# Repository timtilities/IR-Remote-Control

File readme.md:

I have a *Hunter* space heater whose remote control had partially stopped working. The power and mode buttons no longer functioned. Rather than buying a new heater, I decided to take a crack at making a new remote control for it.

***

Some of the buttons still worked, so I setup a [simple IR receiver](https://github.com/Arduino-IRremote/Arduino-IRremote/blob/master/examples/ReceiveDemo/ReceiveDemo.ino) with an Arduino Nano to scan the working button codes. 

The design uses the ATTINY85 MCU and a matrix keypad with 12 buttons (although only 6 are in use for this).  Each button press fires an interrupt to wake the MCU and send the IR signal associated with the button. Once that completes, the MCU goes back into deep sleep. The circuit uses around 30mA while sending and <10nA when sleeping. Assuming 10 button presses per day (over only the winter months), the 2 AAA batteries *should* last more than [5 years](http://oregonembedded.com/batterycalc.htm).  I use NiMH rechargeable batteries removed at the end of each season, so if I have to recharge them once a year I'm happy.

Since I rarely order single PCBs, I designed it with 12 buttons to allow the PCBs to be used in future projects.

The battery clips are Keystone Electronics [55TR](https://www.keyelco.com/product.cfm/product_id/3970), available from [Mouser electronics](https://www.mouser.com/ProductDetail/534-55TR).

The Arduino sketch requires the following libraries:

- [IRremote](https://github.com/Arduino-IRremote/Arduino-IRremote/)
- [Keypad](https://github.com/Chris--A/Keypad)
- [PinChangeInterrupt](https://github.com/NicoHood/PinChangeInterrupt)

The pogo pin adapter is available here:

[https://github.com/timtilities/Pogo-Pin-ICSP-Adapter](https://github.com/timtilities/Pogo-Pin-ICSP-Adapter)

The Case has been designed to be 3D printed, including multicolored buttons. I used the [Z-hop multi-colored printing method](https://www.youtube.com/watch?v=0Sla-vIsvh4) to print the buttons in multiple colors. The top and bottom snap together around the electronics, and the battery cover uses a tab/screw combination to secure it into place. The M3 knurled heat-set insert can be purchased [from Amazon](https://www.amazon.com/dp/B0BW1YP5VQ?psc=1&ref=ppx_yo2ov_dt_b_product_details).

There is an alternative bottom design without the battery cover. It simply snaps together with the top.

Some additional pics at various points in the design and assembly stages:

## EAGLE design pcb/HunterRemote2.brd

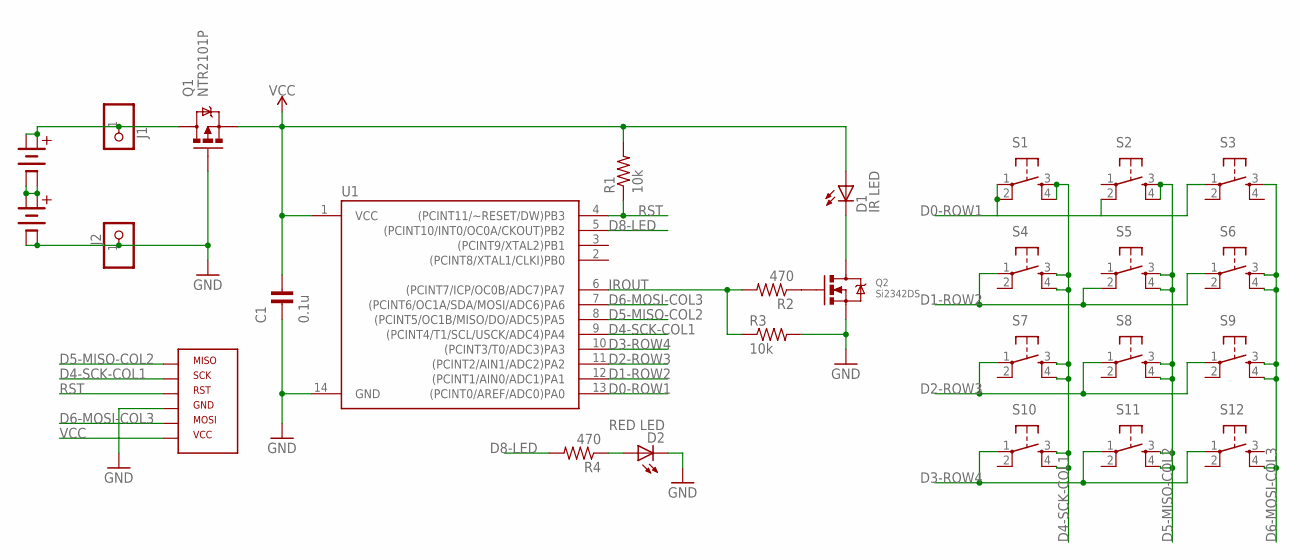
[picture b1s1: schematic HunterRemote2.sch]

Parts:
B1, B2: BATTERYAAA-KEYSTONE-55TR; KEYSTONE_55TR_AAA
C1: 0.1u; C0805
D1: IR LED; LED5MM-90
D2: RED LED; LED-0805-RED
J1, J2: PINHD-1X1; 1X01
Q1: NTR2101P; SOT23-3A
Q2: Si2342DS; SOT23-3A
R1, R3: 10k; R0805
R2, R4: 470; R0805
S1, S2, S3, S4, S5, S6, S7, S8, S9, S10, S11, S12: TAC_SWITCHSMD_5X5_LOW; TACTILE_SWITCH_SMD_5X5_LOW
U1: ATTINY84; SO14
U$1: AVR_ICSP_6PSTRAIGHT; AVR_ICSP_6P_SMD_V2

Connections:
D0-ROW1: S1.1, S1.2, S2.2, S3.1, U1.13 ((PCINT0/AREF/ADC0)PA0)
D1-ROW2: S4.1, S5.2, S6.1, U1.12 ((PCINT1/AIN0/ADC1)PA1)
D2-ROW3: S7.1, S8.1, S9.1, U1.11 ((PCINT2/AIN1/ADC2)PA2)
D3-ROW4: S10.1, S11.1, S12.1, U1.10 ((PCINT3/T0/ADC3)PA3)
D4-SCK-COL1: S1.3, S1.4, S4.3, S4.4, S7.3, S7.4, S10.3, S10.4, U1.9 ((PCINT4/T1/SCL/USCK/ADC4)PA4), U$1.SCK
D5-MISO-COL2: S2.3, S2.4, S5.3, S5.4, S8.3, S8.4, S11.3, S11.4, U1.8 ((PCINT5/OC1B/MISO/DO/ADC5)PA5), U$1.MISO
D6-MOSI-COL3: S3.3, S6.3, S6.4, S9.3, S9.4, S12.4, U1.7 ((PCINT6/OC1A/SDA/MOSI/ADC6)PA6), U$1.MOSI
D8-LED: R4.2, U1.5 ((PCINT10/INT0/OC0A/CKOUT)PB2)
GND: B1.NEG1, B1.NEG2, C1.1, D2.C, J2.1, Q1.1 (G), Q2.2 (S), R3.2, U1.14 (GND), U$1.GND
IROUT: R2.2, R3.1, U1.6 ((PCINT7/ICP/OC0B/ADC7)PA7)
unnamed: B2.POS1, B2.POS2, J1.1, Q1.3 (D)
unnamed: Q2.1 (G), R2.1
unnamed: D1.C, Q2.3 (D)
unnamed: B1.POS1, B1.POS2, B2.NEG1, B2.NEG2
unnamed: D2.A, R4.1
RST: R1.1, U1.4 ((PCINT11/~RESET/DW)PB3), U$1.RST
VCC: C1.2, D1.A, Q1.2 (S), R1.2, U1.1 (VCC), U$1.VCC

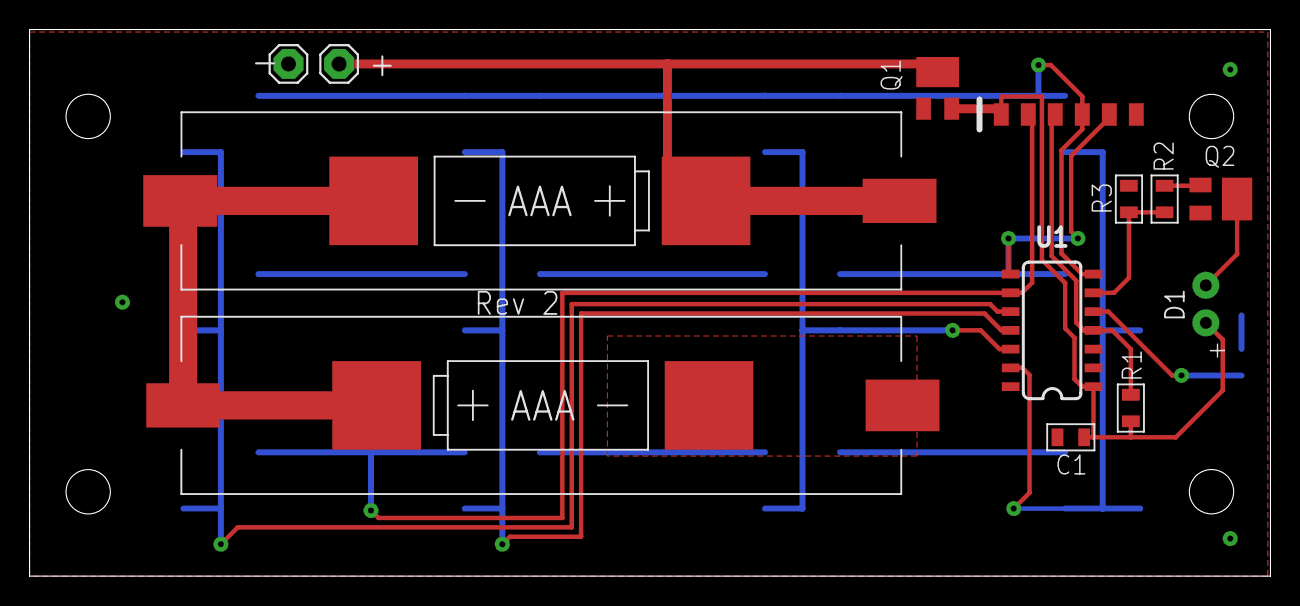
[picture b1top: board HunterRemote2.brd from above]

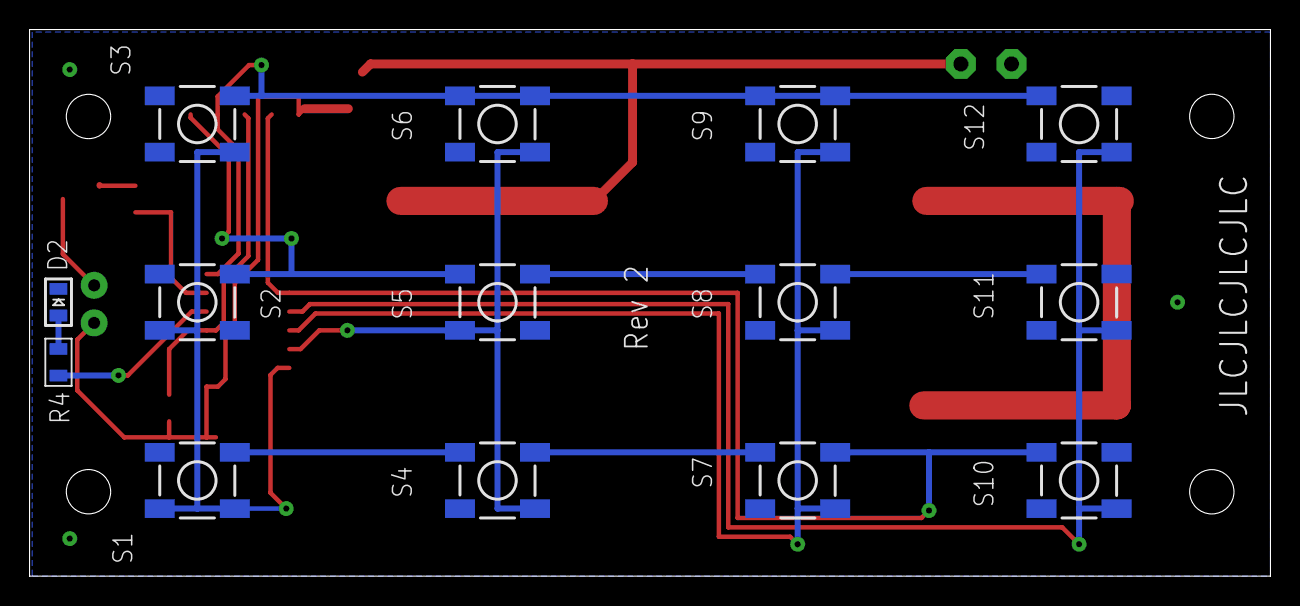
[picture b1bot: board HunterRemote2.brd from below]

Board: 2 copper layers, 84.0 x 37.0 mm, 27 parts (14 on the bottom side), 17 nets.

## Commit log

2026-03-22 initial

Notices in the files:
parts and their libraries:
SparkFun-PowerSymbols: Licensing: Creative Commons ShareAlike 4.0 International - https://creativecommons.org/licenses/by-sa/4.0
